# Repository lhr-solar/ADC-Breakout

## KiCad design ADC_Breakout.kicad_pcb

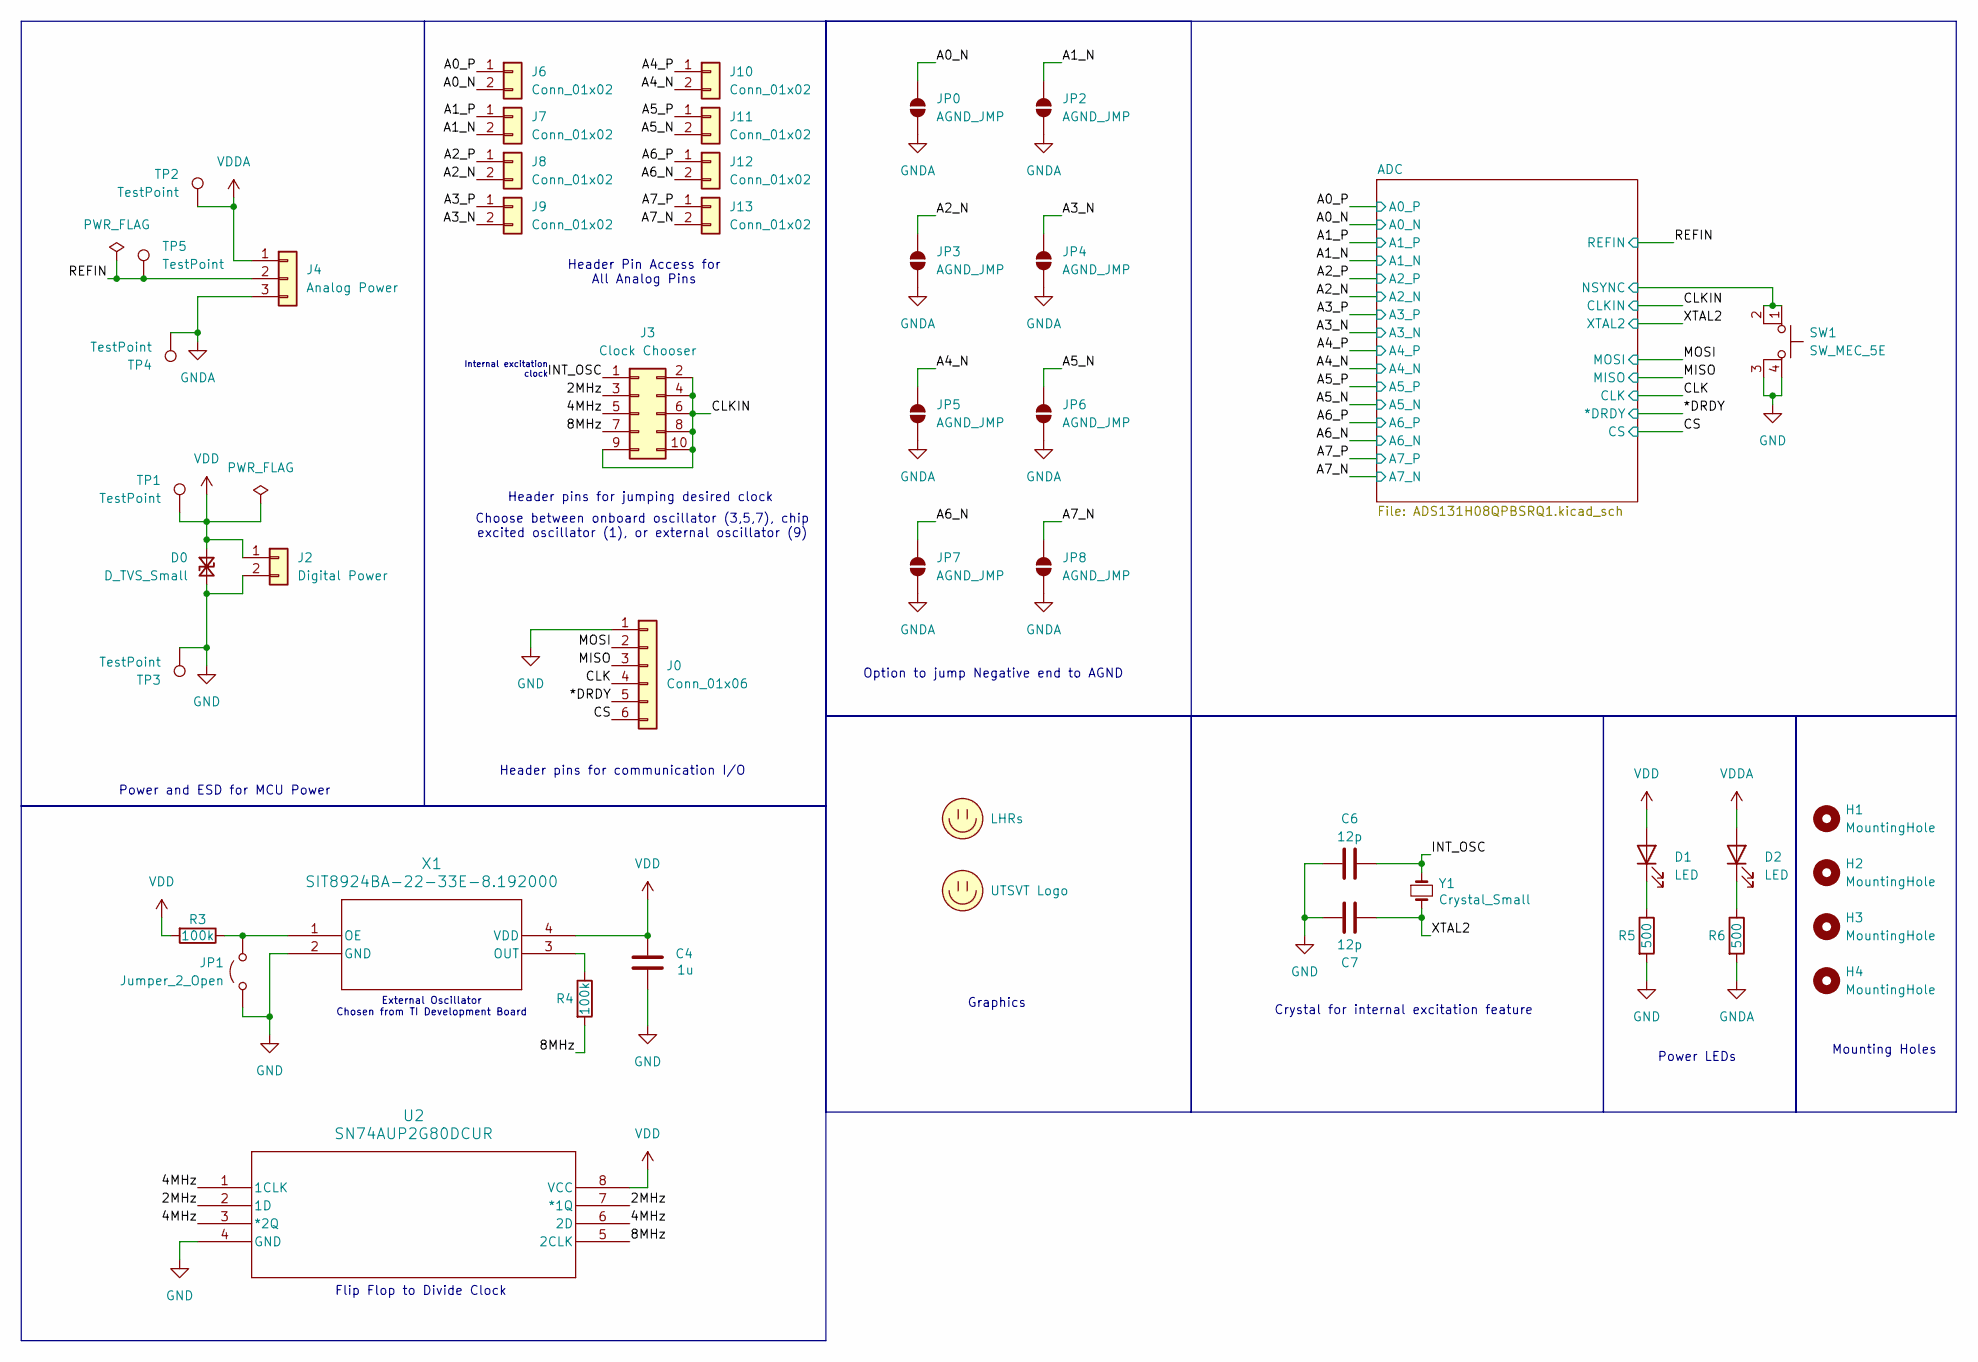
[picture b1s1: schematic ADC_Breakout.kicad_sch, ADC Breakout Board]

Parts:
C4: 1u; C_0805_2012Metric
C6, C7: 12p; C_0805_2012Metric
D0: D_TVS_Small; VAR_CG0603MLU-3.3E
D1, D2: LED; LED_0805_2012Metric
H1, H2, H3, H4: MountingHole; MountingHole_3mm
J0: Conn_01x06; PinHeader_1x06_P2.54mm_Vertical
J2: Digital Power; PinHeader_1x02_P2.54mm_Vertical
J3: Clock Chooser; PinHeader_2x05_P2.54mm_Vertical
J4: Analog Power; PinHeader_1x03_P2.54mm_Vertical
J6, J7, J8, J9, J10, J11, J12, J13: Conn_01x02; PinHeader_1x02_P2.54mm_Vertical
JP0, JP2, JP3, JP4, JP5, JP6, JP7, JP8: AGND_JMP; SolderJumper-2_P1.3mm_Open_TrianglePad1.0x1.5mm
JP1: Jumper_2_Open; PinHeader_1x02_P2.54mm_Vertical
LOGO0: LHRs; LHRs_LOGO
LOGO1: UTSVT Logo; UTSVT_Logo_Symbol
R3, R4: 100k; R_0805_2012Metric
R5, R6: 500; R_0805_2012Metric
SW1: SW_MEC_5E; SW_B3SL-1002P_OMR
TP1, TP2, TP3, TP4, TP5: TestPoint; TestPoint_HEX_3mmID
U2: SN74AUP2G80DCUR; DCU8
X1: SIT8924BA-22-33E-8.192000; SMD4_SIT8924B_3P2X2P5X0P75_SIT
Y1: Crystal_Small; Crystal_SMD_TXC_7A-2Pin_5x3.2mm

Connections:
/2MHz: J3.3, U2.2 (1D), U2.7 (*1Q)
/4MHz: J3.5, U2.1 (1CLK), U2.3 (*2Q), U2.6 (2D)
/8MHz: J3.7, R4.2, U2.5 (2CLK)
/*DRDY: J0.5; also elsewhere on the board
/A0_N: J6.2, JP0.1 (A); also elsewhere on the board
/A0_P: J6.1; also elsewhere on the board
/A1_N: J7.2, JP2.1 (A); also elsewhere on the board
/A1_P: J7.1; also elsewhere on the board
/A2_N: J8.2, JP3.1 (A); also elsewhere on the board
/A2_P: J8.1; also elsewhere on the board
/A3_N: J9.2, JP4.1 (A); also elsewhere on the board
/A3_P: J9.1; also elsewhere on the board
/A4_N: J10.2, JP5.1 (A); also elsewhere on the board
/A4_P: J10.1; also elsewhere on the board
/A5_N: J11.2, JP6.1 (A); also elsewhere on the board
/A5_P: J11.1; also elsewhere on the board
/A6_N: J12.2, JP7.1 (A); also elsewhere on the board
/A6_P: J12.1; also elsewhere on the board
/A7_N: J13.2, JP8.1 (A); also elsewhere on the board
/A7_P: J13.1; also elsewhere on the board
/ADC/NSYNC: SW1.1, SW1.2; also elsewhere on the board
/CLK: J0.4; also elsewhere on the board
/CLKIN: J3.2, J3.4, J3.6, J3.8, J3.9, J3.10; also elsewhere on the board
/CS: J0.6; also elsewhere on the board
/INT_OSC: C6.1, J3.1, Y1.1
/MISO: J0.3; also elsewhere on the board
/MOSI: J0.2; also elsewhere on the board
/REFIN: J4.2, TP5.1; also elsewhere on the board
/XTAL2: C7.1, Y1.2; also elsewhere on the board
GND: C4.1, C6.2, C7.2, D0.2 (A2), J0.1, J2.2, JP1.1 (A), R5.2, SW1.3 (K), SW1.4 (A), TP3.1, U2.4 (GND), X1.2 (GND); also elsewhere on the board
GNDA: J4.3, JP0.2 (B), JP2.2 (B), JP3.2 (B), JP4.2 (B), JP5.2 (B), JP6.2 (B), JP7.2 (B), JP8.2 (B), R6.2, TP4.1; also elsewhere on the board
unnamed: D1.1 (K), R5.1
unnamed: D2.1 (K), R6.1
unnamed: JP1.2 (B), R3.1, X1.1 (OE)
unnamed: R4.1, X1.3 (OUT)
VDD: C4.2, D0.1 (A1), D1.2 (A), J2.1, R3.2, TP1.1, U2.8 (VCC), X1.4 (VDD); also elsewhere on the board
VDDA: D2.2 (A), J4.1, TP2.1; also elsewhere on the board

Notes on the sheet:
Choose between onboard oscillator (3,5,7), chip excited oscillator (1), or external oscillator (9)
Header pins for jumping desired clock
Flip Flop to Divide Clock
Graphics
External Oscillator Chosen from TI Development Board
Mounting Holes
Internal excitation clock
Option to jump Negative end to AGND
Crystal for internal excitation feature
Header Pin Access for All Analog Pins
Power and ESD for MCU Power
Header pins for communication I/O
Power LEDs

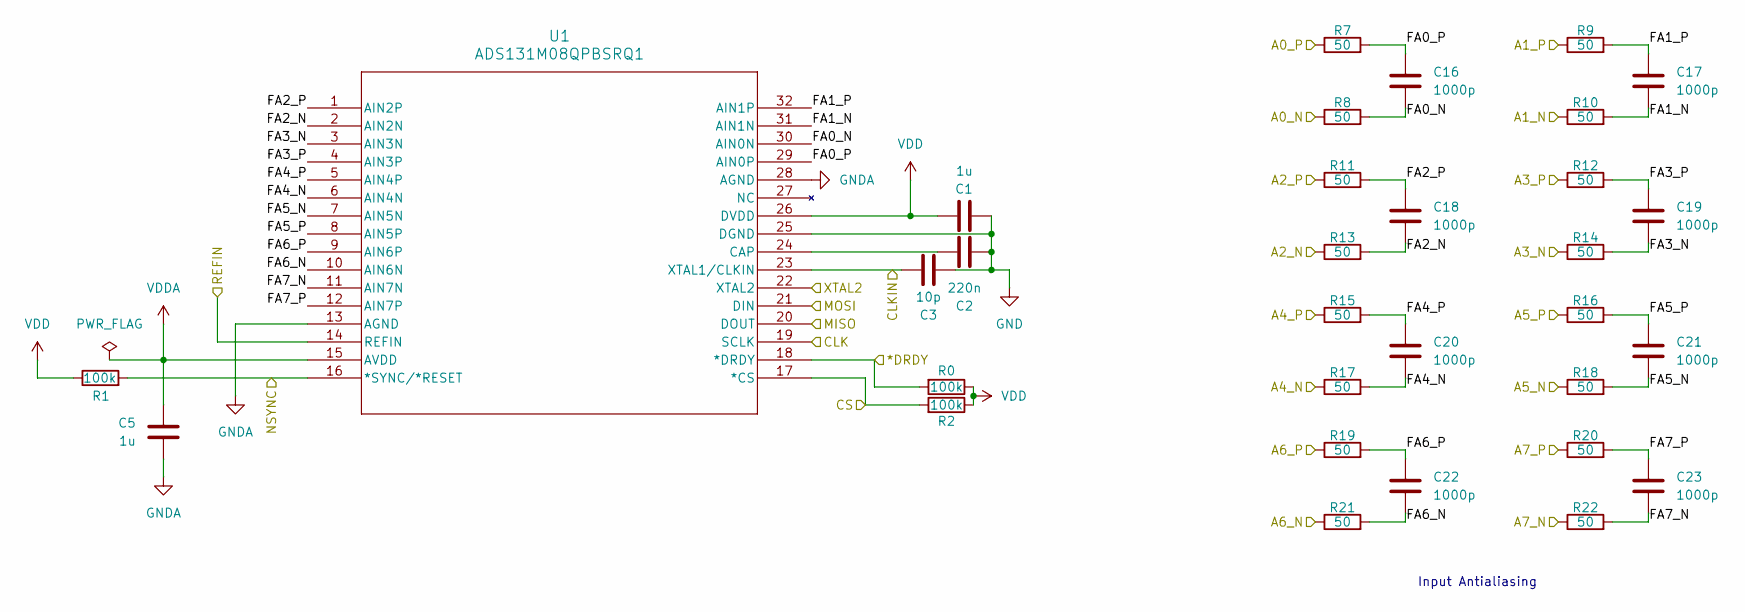
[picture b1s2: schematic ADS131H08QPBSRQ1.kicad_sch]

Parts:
C1, C5: 1u; C_0805_2012Metric
C2: 220n; C_0805_2012Metric
C3: 10p; C_0805_2012Metric
C16, C17, C18, C19, C20, C21, C22, C23: 1000p; C_0805_2012Metric
R0, R1, R2: 100k; R_0805_2012Metric
R7, R8, R9, R10, R11, R12, R13, R14, R15, R16, R17, R18, R19, R20, R21, R22: 50; R_0805_2012Metric
U1: ADS131M08QPBSRQ1; TQFP32_PBS_TEX

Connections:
/*DRDY: R0.2, U1.18 (*DRDY); also elsewhere on the board
/A0_N: R8.1; also elsewhere on the board
/A0_P: R7.1; also elsewhere on the board
/A1_N: R10.1; also elsewhere on the board
/A1_P: R9.1; also elsewhere on the board
/A2_N: R13.1; also elsewhere on the board
/A2_P: R11.1; also elsewhere on the board
/A3_N: R14.1; also elsewhere on the board
/A3_P: R12.1; also elsewhere on the board
/A4_N: R17.1; also elsewhere on the board
/A4_P: R15.1; also elsewhere on the board
/A5_N: R18.1; also elsewhere on the board
/A5_P: R16.1; also elsewhere on the board
/A6_N: R21.1; also elsewhere on the board
/A6_P: R19.1; also elsewhere on the board
/A7_N: R22.1; also elsewhere on the board
/A7_P: R20.1; also elsewhere on the board
/ADC/FA0_N: C16.1, R8.2, U1.30 (AIN0N)
/ADC/FA0_P: C16.2, R7.2, U1.29 (AIN0P)
/ADC/FA1_N: C17.1, R10.2, U1.31 (AIN1N)
/ADC/FA1_P: C17.2, R9.2, U1.32 (AIN1P)
/ADC/FA2_N: C18.1, R13.2, U1.2 (AIN2N)
/ADC/FA2_P: C18.2, R11.2, U1.1 (AIN2P)
/ADC/FA3_N: C19.1, R14.2, U1.3 (AIN3N)
/ADC/FA3_P: C19.2, R12.2, U1.4 (AIN3P)
/ADC/FA4_N: C20.1, R17.2, U1.6 (AIN4N)
/ADC/FA4_P: C20.2, R15.2, U1.5 (AIN4P)
/ADC/FA5_N: C21.1, R18.2, U1.7 (AIN5N)
/ADC/FA5_P: C21.2, R16.2, U1.8 (AIN5P)
/ADC/FA6_N: C22.1, R21.2, U1.10 (AIN6N)
/ADC/FA6_P: C22.2, R19.2, U1.9 (AIN6P)
/ADC/FA7_N: C23.1, R22.2, U1.11 (AIN7N)
/ADC/FA7_P: C23.2, R20.2, U1.12 (AIN7P)
/ADC/NSYNC: R1.2, U1.16 (*SYNC/*RESET); also elsewhere on the board
/CLK: U1.19 (SCLK); also elsewhere on the board
/CLKIN: C3.1, U1.23 (XTAL1/CLKIN); also elsewhere on the board
/CS: R2.2, U1.17 (*CS); also elsewhere on the board
/MISO: U1.20 (DOUT); also elsewhere on the board
/MOSI: U1.21 (DIN); also elsewhere on the board
/REFIN: U1.14 (REFIN); also elsewhere on the board
/XTAL2: U1.22 (XTAL2); also elsewhere on the board
GND: C1.2, C2.2, C3.2, U1.25 (DGND); also elsewhere on the board
GNDA: C5.2, U1.13 (AGND), U1.28 (AGND); also elsewhere on the board
unnamed: C2.1, U1.24 (CAP)
VDD: C1.1, R0.1, R1.1, R2.1, U1.26 (DVDD); also elsewhere on the board
VDDA: C5.1, U1.15 (AVDD); also elsewhere on the board

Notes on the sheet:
Input Antialiasing

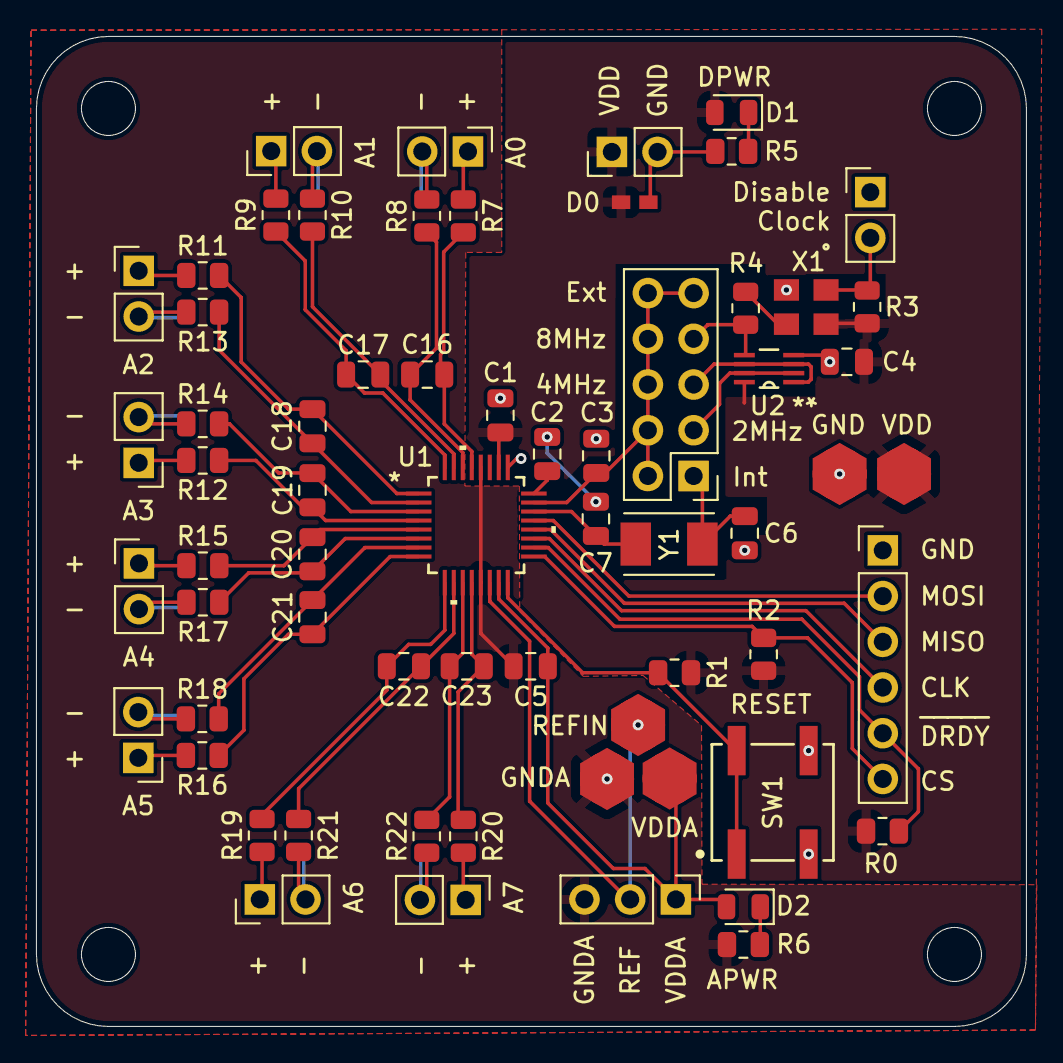
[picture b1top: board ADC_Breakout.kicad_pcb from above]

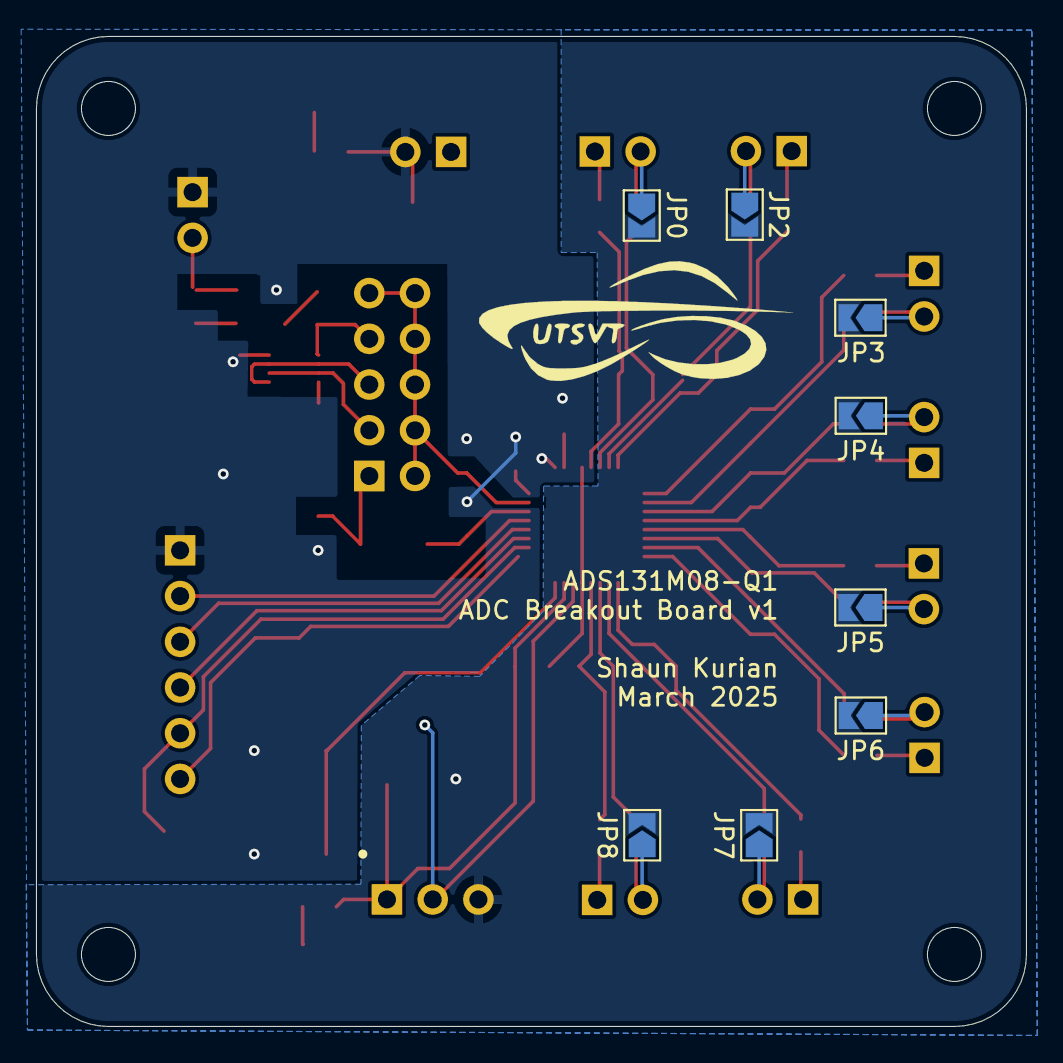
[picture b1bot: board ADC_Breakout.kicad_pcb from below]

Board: 2 copper layers, 55.0 x 55.0 mm, 78 parts (10 on the bottom side), 54 nets.

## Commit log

2025-02-15 initial layout
2025-02-15 slight modification to layout
2025-02-18 Updated explanations for headers
2025-02-18 Added protection
2025-02-18 Updated ESD
2025-02-22 Updated schematic with antialiasing
2025-02-22 New footprints added
2025-02-28 added all files
2025-03-07 Updated Layout
2025-03-08 Layout updates
2025-03-08 Removed lock files
2025-03-08 Added graphics + iBOM
2025-03-08 Updated footprint.
2025-03-08 Added 3d models
2025-03-27 gerebres
